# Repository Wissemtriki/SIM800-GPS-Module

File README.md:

# SIM800 GPS Module

This project presents the **PCB design and implementation** of a SIM800 GSM module integrated with a GPS module using **Altium Designer**.  
It includes the complete Altium project files, schematics, PCB layout, and photos of the assembled module.  
The design enables GSM communication and GPS positioning for embedded applications and IoT devices.

### Tools Used
- Altium Designer
- SIM800 GSM Module
- GPS Module

### Project Contents
- Complete Altium project folder (.PrjPCB, .SchDoc, .PcbDoc, etc.)
- PCB layout files
- Photos of the assembled PCB

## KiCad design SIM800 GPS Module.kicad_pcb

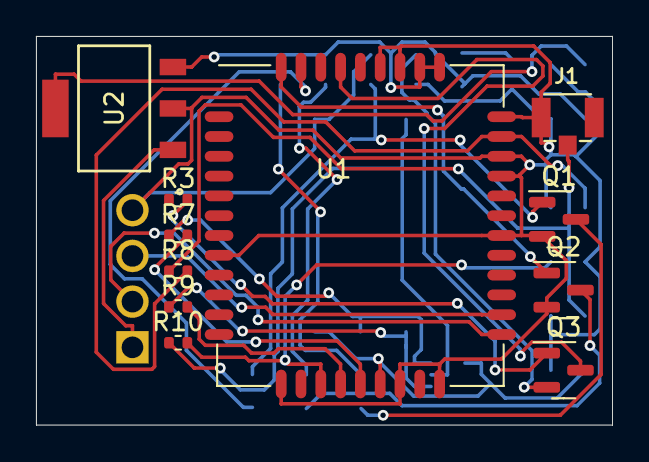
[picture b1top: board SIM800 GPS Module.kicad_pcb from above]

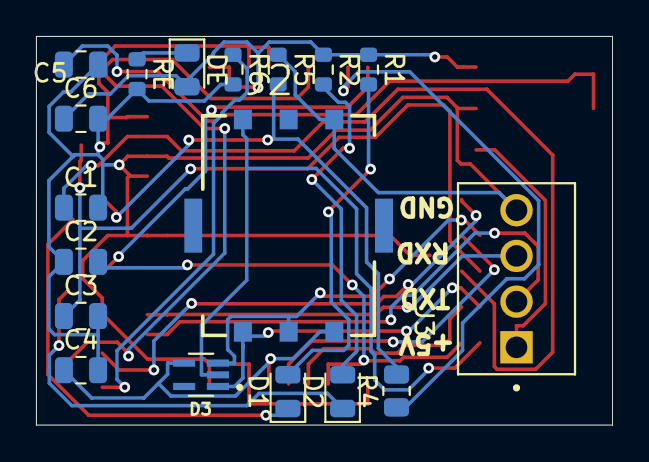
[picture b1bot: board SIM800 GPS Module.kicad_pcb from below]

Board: 2 copper layers, 32.0 x 21.6 mm, 29 parts (18 on the bottom side), 26 nets.

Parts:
C1, C3: 100nF; C_0805_2012Metric
C2: 1nF; C_0805_2012Metric
C4: 10nF; C_0805_2012Metric
C5: 470pF; C_0805_2012Metric
C6: 2.2pF; C_0805_2012Metric
D1, D2: Red LED; LED_0805_2012Metric
D3: ESDA6V1W5; SOT65P210X110-5N
DE: Red LED; LED_0805_2012Metric
J1: U.FL-R-SMT-1_10_; HRS_U.FL-R-SMT-1_10_
J2: SIM8051-6-0-14-00-X-REVD; GCT_SIM8051-6-0-14-00-X-REVD
J3: Conn_01x04; TE_282834-4
Q1, Q2, Q3: BC817; SOT-23
R1, R2: 470; R_0603_1608Metric
R3: 4k7; R_0402_1005Metric
R4: 10k; R_0805_2012Metric
R5, R6: 47K; R_0603_1608Metric
R7, R9, R10: 26.1; R_0402_1005Metric
R8: 0; R_0402_1005Metric
RE: 2k7; R_0603_1608Metric
U1: SIM800C; SIMCom_SIM800C
U2: MIC5209-4.2YS; SOT-223_S_MCL

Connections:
+4.2V: C6.1, DE.2 (A), R1.1, R2.1, U1.34 (VBAT), U1.35 (VBAT), U2.3 (OUT)
+5V: J3.1, U2.1 (IN)
GND: C1.2, C2.1, C3.2, C4.2, C5.2, C6.2, J1.1, J2.C5 (GND), J3.4, Q1.2 (E), Q2.2 (E), R5.1, R6.2, RE.2, U1.8 (GND), U1.13 (GND), U1.19 (GND), U1.21 (GND), U1.27 (GND), U1.30 (GND), U1.31 (GND), U1.33 (GND), U1.36 (GND), U1.37 (GND), U2.2 (GND)
NETLIGHT: R4.1, U1.41 (NETLIGHT)
unnamed: C3.1, J1.2, R8.1
unnamed: C5.1, U2.4
unnamed: D1.2 (A), R1.2
unnamed: D1.1 (K), Q1.3 (C)
unnamed: D2.2 (A), R2.2
unnamed: D2.1 (K), Q2.3 (C)
unnamed: DE.1 (K), RE.1
unnamed: D3.1, J2.C3 (CLK), R9.1
unnamed: D3.2, J2.C7 (I/O), R10.1
unnamed: D3.3, J2.C2 (RST), R7.1
unnamed: C4.1, D3.4, J2.C1 (VCC), U1.18 (SIM_VDD)
unnamed: Q1.1 (B), R4.2, R5.2
unnamed: Q3.1 (B), R3.2
unnamed: Q3.3 (C), U1.39 (~PWRKEY)
unnamed: Q3.2 (E), R6.1
unnamed: C1.1, R8.2, U1.32 (GSM_ANT)
unnamed: R9.2, U1.16 (SIM_CLK)
unnamed: C2.2, R10.2, U1.15 (SIM_DATA)
unnamed: R7.2, U1.17 (SIM_RST)
RXD: J3.3, U1.23 (UART2_RXD)
STATUS: Q2.1 (B), U1.42 (STATUS)
TXD: J3.2, U1.22 (UART2_TXD)

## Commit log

2025-11-13 Initial commit - SIM800 GSM + GPS module PCB design with Altium files and photos
2025-11-13 Add README.md with project overview
